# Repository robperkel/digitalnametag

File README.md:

# E-Paper Digital Nametag

This projects creates a simple re-programmable E-Paper Nametag with the AVR64DU32 microcontroller (MCU). The MCU enumerates as a standard COM serial port when plugged into a computer. 

## Licensing

### Software 
- Code that is automatically generated by MPLAB&reg; Code Configurator (MCC) or pulled from a code example is licensed by Microchip (full agreement is in the header files).
    - The short version is that it is free to use/modify, so long as it uses a Microchip MCU.
- Code that I wrote (firmware and image loading scripts) is licensed under GNU AGPL v3
    - https://choosealicense.com/licenses/agpl-3.0/ 

### Hardware 

- Hardware Design (Schematic and PCB files) are licensed under CERN OHL v2
    - https://choosealicense.com/licenses/cern-ohl-s-2.0/
- 3D models for parts in the PCB are not included due to licensing restrictions. 

## Python Libraries Required (Not Included)

- [Python Image Library (Pillow)](https://pypi.org/project/pillow/)
    - This library opens the image and reads the pixel values.
- [pySerial](https://pypi.org/project/pyserial/)
    - This library allows the script to send data over a COM port.

## Image Configuration  

- Size must be 212 x 104 pixels 
- Colors must only be Red/Black/White
    - The easiest way to achieve this is to use Indexed Color Mode in your image editor
        - Red = 0xFF0000 [255, 0, 0]
        - Black = 0x000000 [0, 0, 0]
        - White = 0xFFFFFF [255, 255, 255]

A test image is provided in the Images folder.

## Programming Connector

This board is designed to use a 6 position Tag-Connect header (such as a [TC2030-ICESPI](https://www.tag-connect.com/product/tc2030-icespi-legged-cable-for-use-with-atmel-ice)) for programming. 

It should be possible to carefully solder wires to the same programming pads to program without this connector, although this may prevent the use of a Tag-Connect header in the future due to the uneven surface created.

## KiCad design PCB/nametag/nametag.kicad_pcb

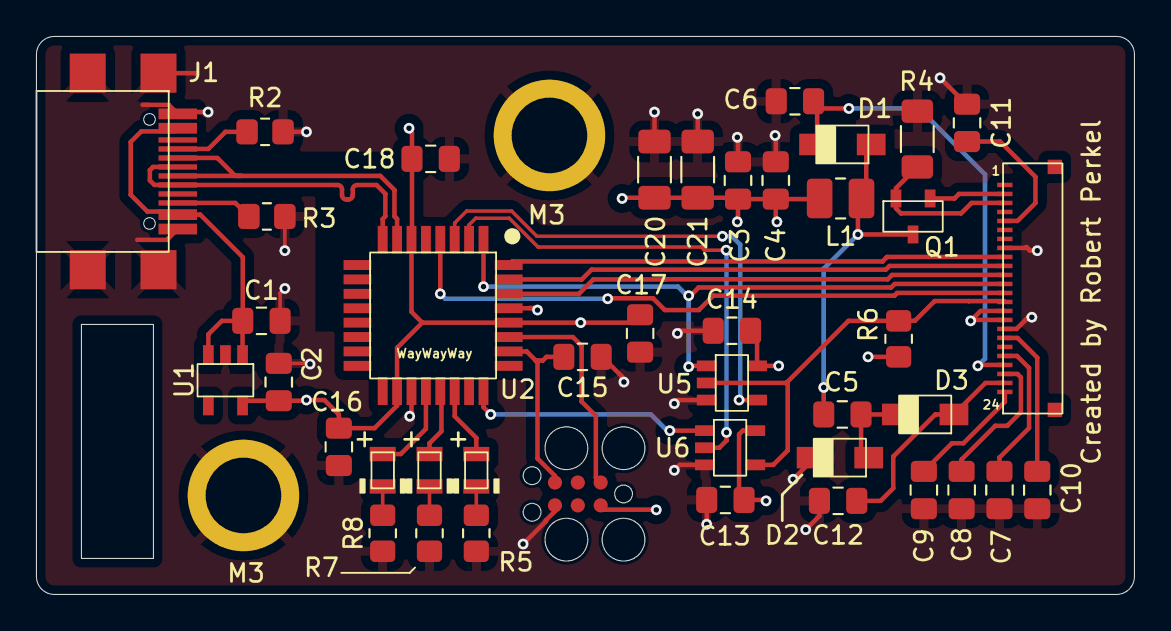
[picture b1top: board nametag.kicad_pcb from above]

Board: 4 copper layers, 61.0 x 31.0 mm, 42 parts (0 on the bottom side), 35 nets.

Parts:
C1, C4, C6, C7, C8, C9, C10, C11, C12: 1uF, 25V; C_0805_2012Metric_Pad1.18x1.45mm_HandSolder
C2: 2.2uF; C_0805_2012Metric_Pad1.18x1.45mm_HandSolder
C3, C13, C14, C15, C16, C18: 0.1uF, 16V; C_0805_2012Metric_Pad1.18x1.45mm_HandSolder
C5: 4.7uF/25V; C_0805_2012Metric_Pad1.18x1.45mm_HandSolder
C17: 10nF; C_0805_2012Metric_Pad1.18x1.45mm_HandSolder
C20, C21: 10uF; C_1206_3216Metric_Pad1.33x1.80mm_HandSolder
D1, D2, D3: PMEG3020ER; SOD-123W
D4, D5, D6: LED; LED 0805
J1: GSB1C41110SSHR
J2: FH34SRJ-24S-0.5SH
J3: Conn_02x03_Odd_Even; TC2030-IDC-FP
L1: 10uH; L_1008_2520Metric_Pad1.43x2.20mm_HandSolder
Q1: NXV55UN; SOT23-3
R2, R3: 5.1k; R_0805_2012Metric_Pad1.20x1.40mm_HandSolder
R4: 0.47, 0.5W; R_1206_3216Metric_Pad1.30x1.75mm_HandSolder
R5, R7, R8: 470; R_0805_2012Metric_Pad1.20x1.40mm_HandSolder
R6: 100k; R_0805_2012Metric_Pad1.20x1.40mm_HandSolder
U1: MIC550x; SOT23-5
U2: AVR64DU32; 7x7 TQFP-32 (PT)
U5, U6: SN74LV1T125DBV; SOT23-5

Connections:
+3.3V: C2.2, C3.1, C4.1, C13.1, C14.1, C16.1, C17.1, C18.1, C20.2, C21.2, J2.15 (VDDIO), J2.16 (VDDA), J3.2, L1.1, U1.5 (OUT), U2.6 (VUSB), U2.18 (VDD), U2.28 (VDD), U5.5 (VCC), U6.5 (VCC)
+5V: C1.1, J1.A4 (VBUS), J1.B4 (VBUS), U1.1 (IN), U1.3 (EN)
/D+: J1.A6 (D+), J1.B6 (D+), U2.8 (D+)
/D-: J1.A7 (D-), J1.B7 (D-), U2.7 (D-)
D/C: J2.11 (D/C), U2.30 (PA0)
GND: C1.2, C2.1, C3.2, C4.2, C6.1, C7.1, C8.1, C9.1, C10.1, C11.1, C12.1, C13.2, C14.2, C15.2, C16.2, C17.2, C18.2, C20.1, C21.1, D2.1 (K), J1.A1 (GND), J1.B1 (GND), J1.S1 (SHIELD), J2.8 (BS), J2.17 (GND), J3.6, R2.2, R3.2, R4.1, R5.1, R6.2, R7.1, R8.1, U1.2 (GND), U2.19 (VSS), U2.29 (VSS), U5.3 (GND), U6.3 (GND)
LED_DISP: D4.2 (A), U2.22 (PF2)
LED_MEM: D5.2 (A), U2.21 (PF1)
LED_USB: D6.2 (A), U2.20 (PF0)
MISO: U2.3 (PA5), U5.4 (Y)
MOSI: U2.2 (PA4), U6.2 (A)
unnamed: C5.2, D1.2 (A), L1.2, Q1.3 (D)
unnamed: C6.2, D1.1 (K), J2.21 (VGH)
unnamed: C5.1, D2.2 (A), D3.1 (K)
unnamed: C12.2, D3.2 (A), J2.23 (VGL)
unnamed: D4.1 (K), R5.2
unnamed: D5.1 (K), R7.2
unnamed: D6.1 (K), R8.2
unnamed: J1.A5 (CC1), R2.1
unnamed: J1.B5 (CC2), R3.1
unnamed: J2.2 (GDR), Q1.1 (G)
unnamed: J2.3 (RESE), Q1.2 (S), R4.2
unnamed: C9.2, J2.24 (VCOM)
unnamed: C10.2, J2.18 (VDDD)
unnamed: C7.2, J2.20 (VDH)
unnamed: C11.2, J2.5 (VDHR)
unnamed: C8.2, J2.22 (VDL)
SCLK: J2.13 (SCLK/SCL), U2.4 (PA6)
SDA: J2.14 (SDI/SDA), R6.1, U5.2 (A), U6.4 (Y)
UPDI: J3.1, U2.27 (PF7/UPDI)
~BUSY: J2.9 (~BUSY), U2.32 (PA2)
~DISP_CS: J2.12 (~CS), U2.1 (PA3), U5.1 (~OE)
~DISP_MOSI_EN: U2.24 (PF4), U6.1 (~OE)
~DISP_RESET: J2.10 (~RESET), U2.31 (PA1)
~RESET: C15.1, J3.5, U2.26 (PF6/~RESET)

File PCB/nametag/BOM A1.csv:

"Reference","Value","DNP","Footprint","Qty"
"C1,C4,C6,C7,C8,C9,C10,C11,C12","1uF, 25V","","Capacitor_SMD:C_0805_2012Metric_Pad1.18x1.45mm_HandSolder","9"
"C2","2.2uF","","Capacitor_SMD:C_0805_2012Metric_Pad1.18x1.45mm_HandSolder","1"
"C3,C13,C14,C15,C16,C18","0.1uF, 16V","","Capacitor_SMD:C_0805_2012Metric_Pad1.18x1.45mm_HandSolder","6"
"C5","4.7uF/25V","","Capacitor_SMD:C_0805_2012Metric_Pad1.18x1.45mm_HandSolder","1"
"C17","10nF","","Capacitor_SMD:C_0805_2012Metric_Pad1.18x1.45mm_HandSolder","1"
"C19,C23","0.1uF, 16V","DNP","Capacitor_SMD:C_0805_2012Metric_Pad1.18x1.45mm_HandSolder","2"
"C20,C21","10uF","DNP","Capacitor_SMD:C_1206_3216Metric_Pad1.33x1.80mm_HandSolder","2"
"CLR0,CLR1,CLR2,R9,SIZE0,SIZE1,SIZE2,SIZE3","0","DNP","Resistor_SMD:R_0603_1608Metric_Pad0.98x0.95mm_HandSolder","8"
"D1,D2,D3","PMEG3020ER","","StandardPackages_Custom:SOD-123W","3"
"D4,D5,D6","LED","","StandardPackages_Custom:LED 0805","3"
"J1","USB_C_Receptacle_USB2.0_14P","","nametag:12402012E212A","1"
"J2","~","","nametag:FH34SRJ-24S-0.5SH","1"
"L1","10uH","","Inductor_SMD:L_1008_2520Metric_Pad1.43x2.20mm_HandSolder","1"
"Q1","NXV55UN","","StandardPackages_Custom:SOT23-3","1"
"R1","0","","Resistor_SMD:R_0805_2012Metric_Pad1.20x1.40mm_HandSolder","1"
"R2,R3","5.1k","","Resistor_SMD:R_0805_2012Metric_Pad1.20x1.40mm_HandSolder","2"
"R4","0.47, 0.5W","","Resistor_SMD:R_1206_3216Metric_Pad1.30x1.75mm_HandSolder","1"
"R5,R7,R8","470","","Resistor_SMD:R_0805_2012Metric_Pad1.20x1.40mm_HandSolder","3"
"R6","100k","","Resistor_SMD:R_0805_2012Metric_Pad1.20x1.40mm_HandSolder","1"
"U1","MIC550x","","StandardPackages_Custom:SOT23-5","1"
"U2","AVR64DU32","","Microchip:7x7 TQFP-32 (PT)","1"
"U3","23K640","DNP","Microchip:TSSOP-8 (ST)","1"
"U4","MCP9700x-ETT","DNP","StandardPackages_Custom:SOT23-3","1"
"U5,U6","SN74LV1T125DBV","","StandardPackages_Custom:SOT23-5","2"

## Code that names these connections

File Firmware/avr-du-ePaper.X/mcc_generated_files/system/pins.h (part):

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
/**
 * @ingroup  pinsdriver
 * @brief Default Interrupt Handler for DISP_RESET pin. 
 *        This is a predefined interrupt handler to be used together with the DISP_RESET_SetInterruptHandler() method.
 *        This handler is called every time the DISP_RESET ISR is executed. 
 * @pre PIN_MANAGER_Initialize() has been called at least once
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
/**
 * @ingroup  pinsdriver
 * @brief Interrupt Handler Setter for DISP_RESET pin input-sense-config functionality.
 *        Allows selecting an interrupt handler for DISP_RESET at application runtime
 * @pre PIN_MANAGER_Initialize() has been called at least once
 * @param InterruptHandler function pointer.
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
/**
 * @ingroup  pinsdriver
 * @brief Default Interrupt Handler for DISP_CS pin. 
 *        This is a predefined interrupt handler to be used together with the DISP_CS_SetInterruptHandler() method.
 *        This handler is called every time the DISP_CS ISR is executed. 
 * @pre PIN_MANAGER_Initialize() has been called at least once
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
/**
 * @ingroup  pinsdriver
 * @brief Interrupt Handler Setter for DISP_CS pin input-sense-config functionality.
 *        Allows selecting an interrupt handler for DISP_CS at application runtime
 * @pre PIN_MANAGER_Initialize() has been called at least once
 * @param InterruptHandler function pointer.
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
/**
 * @ingroup  pinsdriver
 * @brief Default Interrupt Handler for LED_USB pin. 
 *        This is a predefined interrupt handler to be used together with the LED_USB_SetInterruptHandler() method.
 *        This handler is called every time the LED_USB ISR is executed. 
 * @pre PIN_MANAGER_Initialize() has been called at least once
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
/**
 * @ingroup  pinsdriver
 * @brief Interrupt Handler Setter for LED_USB pin input-sense-config functionality.
 *        Allows selecting an interrupt handler for LED_USB at application runtime
 * @pre PIN_MANAGER_Initialize() has been called at least once
 * @param InterruptHandler function pointer.
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
/**
 * @ingroup  pinsdriver
 * @brief Default Interrupt Handler for LED_MEM pin. 
 *        This is a predefined interrupt handler to be used together with the LED_MEM_SetInterruptHandler() method.
 *        This handler is called every time the LED_MEM ISR is executed. 
 * @pre PIN_MANAGER_Initialize() has been called at least once
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
/**
 * @ingroup  pinsdriver
 * @brief Interrupt Handler Setter for LED_MEM pin input-sense-config functionality.
 *        Allows selecting an interrupt handler for LED_MEM at application runtime
 * @pre PIN_MANAGER_Initialize() has been called at least once
 * @param InterruptHandler function pointer.
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
/**
 * @ingroup  pinsdriver
 * @brief Default Interrupt Handler for LED_DISP pin. 
 *        This is a predefined interrupt handler to be used together with the LED_DISP_SetInterruptHandler() method.
 *        This handler is called every time the LED_DISP ISR is executed. 
 * @pre PIN_MANAGER_Initialize() has been called at least once
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
/**
 * @ingroup  pinsdriver
 * @brief Interrupt Handler Setter for LED_DISP pin input-sense-config functionality.
 *        Allows selecting an interrupt handler for LED_DISP at application runtime
 * @pre PIN_MANAGER_Initialize() has been called at least once
 * @param InterruptHandler function pointer.
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
/**
 * @ingroup  pinsdriver
 * @brief Default Interrupt Handler for DISP_MOSI_EN pin. 
 *        This is a predefined interrupt handler to be used together with the DISP_MOSI_EN_SetInterruptHandler() method.
 *        This handler is called every time the DISP_MOSI_EN ISR is executed. 
 * @pre PIN_MANAGER_Initialize() has been called at least once
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
/**
 * @ingroup  pinsdriver
 * @brief Interrupt Handler Setter for DISP_MOSI_EN pin input-sense-config functionality.
 *        Allows selecting an interrupt handler for DISP_MOSI_EN at application runtime
 * @pre PIN_MANAGER_Initialize() has been called at least once
 * @param InterruptHandler function pointer.
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
/**
 * @ingroup  pinsdriver
 * @brief Default Interrupt Handler for IO_PF7 pin. 
 *        This is a predefined interrupt handler to be used together with the IO_PF7_SetInterruptHandler() method.
 *        This handler is called every time the IO_PF7 ISR is executed. 
 * @pre PIN_MANAGER_Initialize() has been called at least once
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
/**
 * @ingroup  pinsdriver
 * @brief Interrupt Handler Setter for IO_PF7 pin input-sense-config functionality.
 *        Allows selecting an interrupt handler for IO_PF7 at application runtime
 * @pre PIN_MANAGER_Initialize() has been called at least once
 * @param InterruptHandler function pointer.
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
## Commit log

2024-05-05 Added new firmware
2024-05-16 Schematic complete
2024-05-17 PCB WIP
2024-05-19 PCB files. BOM. Step model.
2024-05-20 C# Software
2024-05-28 More progress on epaper tool
2024-06-01 Implemented Pixel Manager
2024-06-08 Firmware enhancements. C# Code changes
2024-06-08 Add USB TX Queue
2024-06-16 Created common SPI library
2024-06-16 Preparing for 4 color support
2024-08-10 Cleaned-up repository
2024-08-10 Fixed image
2024-08-10 README edits. Added renders and BOM
2024-08-10 Readme + Test Pattern

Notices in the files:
Firmware/avr-du-ePaper.X/mcc_generated_files/system/pins.h:
© [2024] Microchip Technology Inc. and its subsidiaries.
